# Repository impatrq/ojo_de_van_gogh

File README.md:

# Ojo de van gogh

Este proyecto esta hecho con el fin de crear un **sistema de ayuda a la gente con discapacidad visual** para, a través de inteligencia artificial, **reconocer objectos que no pueden ver**. 

Se compone de un sistema electrónico que va colocado en el antebrazo y lleva una camera que se coloca en la mano. Cuando el ciego, por ejemplo, parpadea dos veces el sensor cerebral entiende su intencionalidad de querer sacar una foto y se lo comunica a la raspberry, esta actua sacando una foto y la procesa con **google vision API** para luego dar una respuesta del texto que se lee en la foto, el objeto que aparece o los colores predominantes

## Requisitos

Para ejecutar este proyecto se debe contar con estos requisitos:

- Hardware: elementos electronicos fisicos para crear el sistema.
  - Mindwave
  - Arduino Nano
  - Raspberry Pi Zero
  - Pi camera
  - Cargador portatil pequeño (ver PCB)
  - Dos buzzers
- Software: lenguajes requeridos para poder llevar a cabo esta idea
  - Python 3.7
  - Arduino IDE

## Instalación

#### Raspberry:

Para ejecutar la instalación debemos pararnos en la carpeta raiz del proyecto y ejecutar

```shell
pip install -r requirements.txt
```

Luego de ejecutar esto contamos con las dependencias para que la raspberry trabaje de manera correcta. 

#### Arduino:

Para ejecutar la instalacion procedemos a conectar el arduino a nuestro computador y seleccionamos el puerto correspondiente y enviamos el archivo "mindwave.ino" que se encuentra en la siguiente ruta *ojo_de_van_gogh\placa_electronica\arduino_code*

## Autores de este repositorio 

- **CARRO, Nahuel Agustín** - *PCB, Arduino y Raspberry* - [NahuelCarro](https://github.com/NahuelCarro)
- **PIERRI, Matias Gabriel** - *PCB, Arduino, Raspberry y Case3D* - [matias1379](https://github.com/matias1379)
- **VILARDO, Theo** - *Raspberry* - [TheoVilardo](https://github.com/theovilardo)
- **FONTE, Gonzalo Juan** - *Case3D* - [gonzafonte](https://github.com/gonzafonte)

## Colaboradores

- **MEDINA, Sergio** - *Supervisor desarrollo proyecto* - [sergiomedinaio](https://github.com/sergiomedinaio)

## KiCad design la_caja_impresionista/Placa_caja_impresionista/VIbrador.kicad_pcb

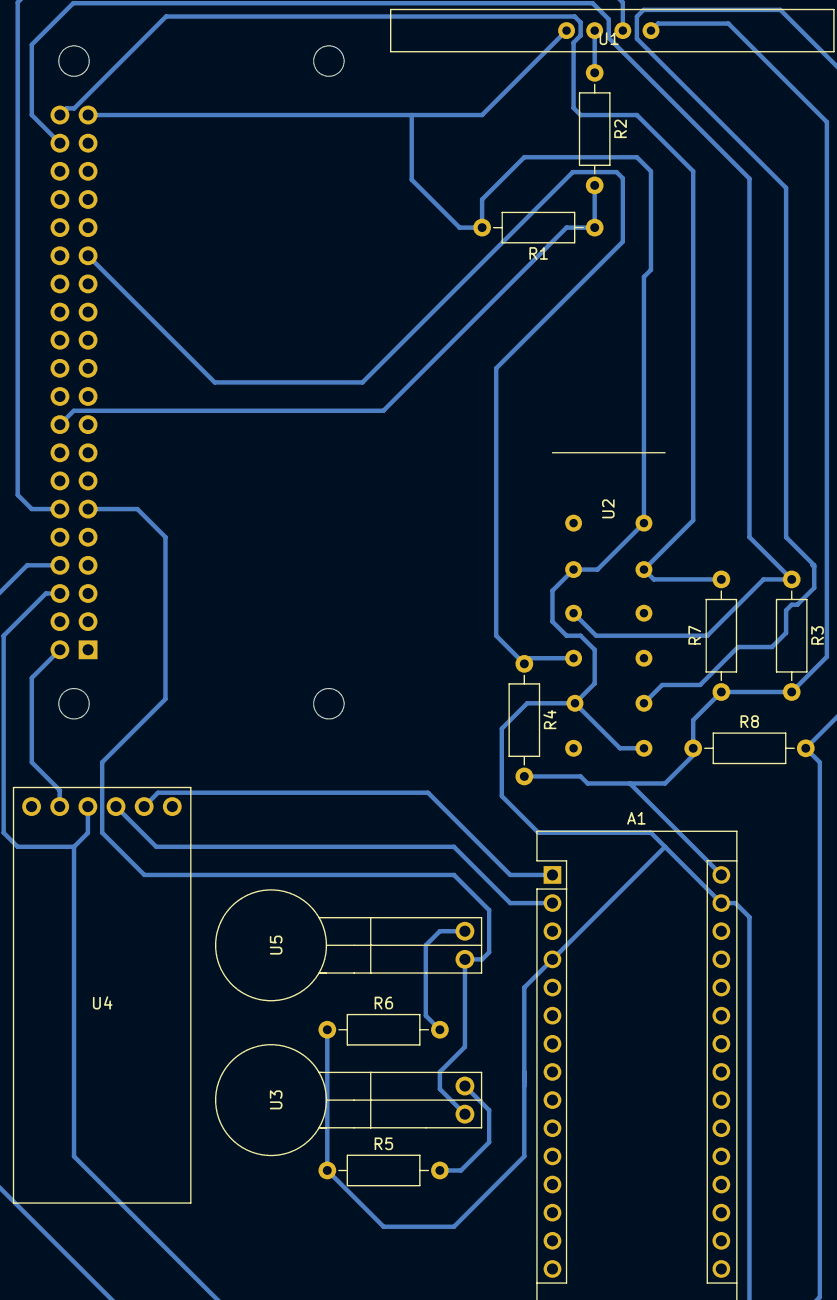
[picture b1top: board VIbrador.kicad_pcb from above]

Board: 2 copper layers, 15 parts (1 on the bottom side), 14 nets.

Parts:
A1: Arduino_Nano_v3.x; Arduino_Nano
R1: 470; R_Axial_DIN0207_L6.3mm_D2.5mm_P10.16mm_Horizontal
R2: 330; R_Axial_DIN0207_L6.3mm_D2.5mm_P10.16mm_Horizontal
R3, R4, R7, R8: 10K; R_Axial_DIN0207_L6.3mm_D2.5mm_P10.16mm_Horizontal
R5, R6: 100; R_Axial_DIN0207_L6.3mm_D2.5mm_P10.16mm_Horizontal
U1: Ultrasonico
U2: Switch-4-posiciones; Switch_4_posiciones
U3, U5: Buzzer; Vibrador
U4: HC-05
U6: PiZeroW; Raspberry_Pi_Zero_Socketed_THT_FaceDown_MountingHoles

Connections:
BUZZER: U3.1, U5.1, U6.11
Echo: R2.1, U1.3
GPIO5: R4.1, U2.7, U6.29
unnamed: R1.1, R2.2, U6.18
unnamed: R5.2, U3.2
unnamed: R6.2, U5.2
OUT+: A1.30, R3.2, R4.2, R7.1, R8.1, U1.1, U4.2, U6.2
OUT-: A1.4, A1.29, R1.2, R5.1, R6.1, U1.4, U2.2, U2.3, U2.9, U2.12, U4.3, U6.6, U6.9, U6.39
RX: A1.1, U4.5
SWITCH-4P: R7.2, U2.4, U6.40
SWITCH-5P: R3.1, U2.5, U6.38
SWITCH-10P: R8.2, U2.10, U6.8
TRIG: U1.2, U6.12
TX: A1.2, U4.4

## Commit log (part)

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2020-04-20 Readme
2020-04-27 Organizamos la disposicion del repositorio
2020-04-27 correccion en el listado de modulos
2020-04-27 Se agrego el readme al repo central
2020-04-27 se agrego el programa que lee los datos de raspberry y vibra segun el color
2020-04-28 Se Creo la carpeta de Diseño_de_estructura, dentro de la misma hay:
    - Dibujos de la estructura del cargador en AutoCAD
    - Dibujos de la estructura del cargador pasado a PDF con rotulo
    - Dibujo del logotipo del proyecto en 3D
    Please enter the commit message for your changes. Lines starting
2020-04-28 Se agrego el modulo de logo al readme
2020-04-28 Se agrego una fotito que explica como va conectado todo que esta piola para tener en cuenta
2020-04-28 se creo la carpeta de campo y se agrego la que teniamos en drive
2020-04-28 se creo la carpeta de cosas utiles que tiene el logo y el rotulo en A4 para AutoCAD
2020-04-30 se borro la aclaracion de que temp es tipo long y usamos la forma dinamica de darse cuenta que tiene python
2020-05-03 se agrego la carpeta con las plaquetas y esquematicos
2020-05-03 se agrego a la carpeta de campo lo que se hizo en la semana del 12/04 al 19/04 (rgb a hsv y mudar la pag)
2020-05-03 se agrego cosas de la semana 25/04 al 3/5 (creamos ig y dejamos la pag con el nuevo theme, trabajamos con gitflow y modelo 3D de placas)
2020-05-03 Agregue la guia que explica pasar de rgb a hsv y hsv a color simple
2020-05-03 Se agregaros las listas del codigo morse y en Sistemas de vibracion se agrego esa lista y su explicacion
2020-05-18 se agrego la feature del case 3D
2020-05-29 Se creo el archivo de la clase detector_colores
2020-05-29 se creo el metodo que transforma de rgb a hsv
2020-05-29 se creo el archivo escribir JSON, y ya esta cosntruida la clase
2020-05-29 Se agrego credencial
2020-05-29 Se agrego el metodo para que se escuchen lo colores
2020-05-29 Se agrego el metodo de audio
2020-05-31 se agregaron la libreria de detector_colores y escribirJson
2020-05-31 se le agrego el while true asi lee todo el tiempo el arduino
2020-06-03 Se actualizó la carpeta de campo
    Se ha agregado todo lo que se hizo de la semana del 25 de mayo hasta el 3 de junio, y tambien se reviso contenido anterior
2020-06-05 Graficador_de-Ondas
    se ajusto los datos para usar el serial ploter dee arduino si necesitas algo
2020-06-08 Se agrego un while que frena el codigo hasta que empiece a entrar informacion distinta de una cadena de caracteres vacios osea " "
2020-06-08 se agrego un bucle for que se repite 4 veces para tomar el valor de relajacion de la persona (4 veces es aproximadamente 4 segundos porque es 1 segundo por muestras)
2020-06-08 Se agrego que retorne el umbral de pestañeo
2020-06-09 Se actualizo carpeta de campo hasta el 9 de junio
    Se ha descripto todo lo que se hizo en la semana
2020-06-09 Se agrego que cuando no este entrando un payload se entienda que no hay informacion entrante
2020-06-10 Una vez que entra un small paquet al while de Esperar mindwave se corta el while ya que se actualiza la variable booleana info que se inicializo en false
2020-06-10 Se metio Calibracion_raw dentro del if de si entra un small packet ya que sino no tiene sentido que devuelva null
2020-06-12 Se hice el esperador de mindwave no detecte el payload sino que solo se fije si entra informacion ya que es imposible que la info sea algo mas que el mindwave
2020-06-18 Se borro unos if que no servian
2020-06-19 Se agregaron cosas que faltaban
2020-06-22 Se pasaron los metodos al cpp
2020-06-22 Codigo lisot para probar en arduino
2020-06-24 Se agrego la carpeta de raspberry python
2020-06-25 Detector de colores por query
    Cargamos una base de 140 colores co sus respectivos RGB y lo que hace es hacer 3 query evaluan que tan parecidos es el RGB de entrada con el RGB de la tabla y el mas parecido lo devuevle asi sabemos 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
2020-06-25 Carpeta librerias
    Aca adentro van a estar las librerias y todo va a juntarse en el main.py
2020-06-25 Se creo un enum para tener codigo mas legible
2020-06-25 Se empezo a limpiar y ordenar el codigo
2020-06-25 Funcion de leer texto agregada
2020-06-25 Se agrego el archivo a analizar
2020-06-25 Se borraron archivos redundantes
2020-06-26 query.py
2020-06-26 Se actualizo la carpeta de campo hasta el 26/6
    Se ha agregado lo que se hizo durante estas dos semandas
2020-06-29 Se soluciono un problema de compatibilidad
2020-06-29 Se puso un if que detecta cuando el query esta vacio. En este caso hace un append al dataframe original para agregarle el nuevo color y deja un mensaje de que hay que clasificarlo. Machine learning p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
2020-07-03 s agrego where que permite fitlrar la nfo con una funcon que devuelva true o false
2020-07-04 Se agrego el codigo de color.py y mas colores en la tabla
    Probe varios colores obtenidos del codigo de color.py y cambie algunas cosas en el codigo de query.py para que cada vez que haya un dataframe vacio me lo guarde y quede en la tabla
2020-07-08 Se hicieron los codigos con base64
    Se hicieron los codigos de color, texto y objetos agregando base 64 para que sea mas rapido
2020-07-08 Se agrego el type a el Raw data y se borro dos variables que no funcionan para nada pero quedaron de copiar y pegar codigo
2020-07-08 Se borro dos variables que se arrastraban por copiar y pegar codigo pero no servian para nada
2020-07-08 Se cambio el nombre a GoogleVisionApi
2020-07-08 Se agrego que pida el dataframe de colores caundo quiere crear un color
2020-07-08 Raw data se borro porque no se usaba era un arrastre de copiar y pegar codigo
2020-07-08 Se termino el metodo para pedir colores
2020-07-08 Funcion de query lista
2020-07-08 Se creo el metodo para leer texto y reproduce el audio
2020-07-08 Cartelito de lo que falta ahcer
2020-07-09 Se agrego para que se ordene de menor a mayor
    Se actualizo el codigo agregando sort_values para que cada vez que haya un nuevo valor quede ordenada la tabla
2020-07-10 Comentado de la funcion pedir color
2020-07-10 Comentario de busqueda binaria
2020-07-13 Actualizacion de carpeta del campo hasta el 13/07
    Se ha puesto todo lo que se ha hecho durante estas dos semanas de trabajo
2020-07-16 Cambios en los TX/RX y buzzer
    Ahora el pin para contorlar el buzzer es el GPIO11 de la raspberry. Ademas el tx/rx del bt va al arduino que le pasa los datos a la raspberry por cable usb. Se borro el modulo para las pilas porque v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
2020-07-16 Nuevos simbolos
    Se creo el simbolo del switch de 4 posiciones y se creo el simbolo del sensor ultrasonico
2020-07-17 Huella Switch de 4 posiciones
    El pitch es de 4mm
2020-07-19 Se creo vibrador.py
    Se agrego los self. a las funciones de punto y linea y se creo el codigo que ejecutara las vibraciones segun el color entrante
2020-07-19 Se creo el codigo para probar la clase
    Se hizo el codigo para probar las vibraciones segun el color que ingrese y se borro la libreria rpi porque no es necesaria
2020-07-21 Conexiones PCB
    Quedo conectado todo feo y como el orto pero esta conectado que es mejor que nada despues hay que revisar todas las conexiones y dejarlas facheras
2020-07-21 Actualizacion esquematico
2020-07-21 Se creo reproductor.py
    Se creo para probar la clase y funciona todo bien, ademas se comento la clase
2020-08-01 Se creo una tabla de colores
    Se encontro una tabla con 860 valores, con sus nombres , hexadecimal y rgb. Se le agrego la columna de id en excel.
2020-08-01 Se actualizo la carpeta de campo
    Se ha actualizado la carpeta de campo hasta lo mas reciente que se ha realizado
2020-08-06 Se import la clase texto_to_audio en el main.py Se creo la instancia reproductor_audio de la clase texto_to_audio Se reemplazo los prints por el metodo "audio" de "texto_to_audio"
2020-08-08 Entrevista de problema a osvaldo
2020-08-09 Se actualizo la funcion reconocer objeto
    Se agrego para que se traduzca cada objeto y te diga el nombre cuando le decis la ubicacion
2020-08-09 Se actualizo el def leer_texto
    Se borro todo lo que ya esta en la clase texto_to audio y se le pasa a esa clase el valor de texto
2020-08-09 Agregue unos resultados mas de la re entrevista
    Volví a llamar para hacer algunas preguntas sobre el color y texto y agregue las conclusiones y lo adapte para que tenga el mismo formato.
    Tambien corregi los tildes de la entrevista de osvaldo.
2020-08-10 Se agrego encuesta a lucila
    Se explica y se da un resumen de los datos que nos contó lucila en su dia a dia y como es la enseñanza para personas con discapacidad visual
2020-09-12 Se creo la clase de colores
    Se ha creado la clase hija colores, que llama a la clase de Googe vision. Luego se ha creado las diferentes funciones para llamar a la api ,obtener los valores de color y los nombres de los mas predo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
2020-09-12 Se agrego la libreria de vibracion
    Se agrego la libreria morse_colores y luego se invoco la funcion para obtener la vibracion de acuerdo al color
2020-09-20 Se ha creado la clase de texto
    Se ha creado la clase para manejar el texto que incluye las funciones para llamar a la api y luego para obtener el valor del texto
2020-09-21 Se corrigieron algunos errores
    Se agrego la clase de google.cloud y se creo la variable de la respuesta de la api
2020-09-23 Se creo la clase de objetos
    Se han creados los metodos para tener la respuesta de la api, tener el objeto y la ubicacion del mismo
2020-09-23 Se cambio los nombres de los metodos de la clase texto
    Se normalizaron los nombres de los metodos para que sean parecidos las 3 clases: color, objetos y texto
2020-09-29 Se hizo un refactoring de la clase de vibracion
    Se crearon los metodos de vibracion en los que se especifica los valores de duracion de la vibracion y el metodo para vibrar segun el color en el que se pasa los valores de punto y linea
2020-10-02 Se realizo el main.py
    Se hizo refactoring del main.py con las clases creadas
2020-10-02 Se agrego para hacer la vibracion con los colores
2020-10-07 Logo 3D
    Este logo 3D es para colocar en nuestros productos y establecer la marca
2020-10-07 Update colores.csv
    se tradujeron los 860 colores
2020-10-07 Rename de la plaqueta
    La plaqueta se llamaba vibrador erroneamente. Paso a llamarse pcb_ojo_de_van_gogh
2020-10-07 Revert "Rename de la plaqueta"
    This reverts commit 4062cc4e7b224c506d507956528a24495f5cce1a.
2020-10-07 Carpeta con codigo arduino
2020-10-07 codigo de vibrador no necesario
2020-10-07 Archivos con nombre viejo borrados
2020-10-07 Carpeta auxiliar
    Los codigos que quedaron de ejemplo que mantuvimos porque nos sirvieron de guia los pasamos a una carpeta auxiliar para ver ejemplos
2020-10-07 Carpetas auxiliares de arduino
2020-10-07 Actualizacion README
    Se actualizo el README principal del proyecto siguiendo un modelo de buenas practicas de documentacion. Se agrego el archivo requirements con dependencias para replicar el proyecto
2020-10-08 Cosas utiles borrada
    Se borro porque no tenia nada interesante adentro
2020-10-08 README estructuras 3D
2020-10-08 README placa electronica
2020-10-14 Se paso de markdown a word
2020-10-16 Se cargaron mas fotos en el word
    Se cargo la foo de la placa con todo el 3D y despues fotos de ejemplos de reconocimeinto de objetos, texto y color
2020-10-16 Carpeta de campo PDF
2020-10-20 Refactoring del main
    Se cambio las importaciones de libreria por el reorden de las carpetas.
    Se puso la ubicacion del dataset de colores con decodificacion utf-8
    Se corrigio para que se tome el enum agregando value.
    Se cambiaron los nombres de los metodos viejos por los actuales
2020-10-24 Borre credenciales de GCP
    Se filtro una credencial de Google Cloud Platform y la elimine porque es informacion sensible
2020-12-15 Se realizo la lectura de la llave para determinar su posición
    Se detecta si la llave esta a la izquierda se hace la lectura del color, si esta la llave en el medio la lectura del texto y si esta a la derecha se hace la lectura del objeto
2020-12-23 Se envia la informacion del parpadeo
    Se cambiaron las funciones para que devuelva el char "1"
